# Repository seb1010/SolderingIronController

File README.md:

# Temperature Controller for Hakko 936 Clone

## Overview
 * PID type controller for regulating the temperature of a soldering iron
 * Control done with lm324 quad opamp
 * Heating element switched with back to back mosfets
 * Switching is done only on voltage zero crossings

## Implementation

### PID Controller
 * Fixed Frequency PWM done at about 6 Hz
 * Signal Path
  1. Active Low-Pass Filter / amplifier
  1. Opamp with compenstion network
  1. PWM circuitry
  1. Zero cross detection

#### Active Low-Pass Filter
 * Purpose
   1. Remove a troublesome 60Hz ripple
   1. Increase the small voltage from the thermistor
 * low voltage was a result of low resistance of thermistor and trying to avoid self-heating or using much power
 * gain is 23 v/v for DC
 * 2 poles at about 11 Hz
 
#### Opamp with compenstaion network
  * Gives +50 degrees of phase shift near crossover
  * Has gain magnitude of about 50 v/v at crossover
  * The previous two things come at the cost of significant gain at 60 Hz which caused problems

#### PWM
  * Nothing interesting here
  * An opamp compares output of previous stage to "triangle like" waveform produced by relaxation oscillator

#### Zero Cross Detection
  * Only triggers on rising edge
  * When transformer voltage crosses zero, a short pulse is sent to a latch
  * The pulse allows the latch to change state if such a thing is "requested" by the PWM circuitry
  * The latch drives the gates of the MOSFET's
  * This configuration is not ideal. It works fine for switching MOSFETs on, but do to the inductance of the transformer the zero crossing of the voltage is not at the zero crossing of the current. So there is still some energy stored in the inductor when the swiches open. This didn't cause any real problems, but it would be nice to get this right.

### Switching
 * The Sources of the MOSFETs were connected together
 * This node was also the cicuit ground
   * This made it very easy to switch mosfets
 * The advantages of using MOSFETs
   * Easy to control
   * Low voltage drop results in high efficiency and no need for heat sinking
 * Used a SQ4946AEY Dual MOSFET
 * The gates are intentionally driven through a large resitor to slow switching times

### Power Supply for Control Circuitry
 * Shunt Zener Regulator
   * used a current source in place of usual resitor due to issues caused by 60 Hz ripple on supply rail
 * avoided electrolytic capacitors bc the the case can get quite warm

### PCB
* Had to fit in existing case
* Double sided
* Ordered from prototyping service (JLC PCB)
* I had to hand-solder everything

* Connected to existing case with M3 screws and bits of metal cut from a can
  * This may seem crude, but the board stays in place. Also the can is too flexible to put much stress on the board, so chip capacitors are unlikely to crack.

## Results
 * It seems to provide excellent regulation of the heating element temperature, but in this isn't enough to make a great soldering iron. I believe this system is let down by poor coupling between heating element and  the actual tip.

In the above picture the reference voltage was changed a little and the controller was able to adjust the temperature of the heating element with minimal overshoot in just a few hundred milliseconds. Channel 1 is the Gate Source voltage of the MOSFETs and Channel 2 is the input to the PWM "comparator".

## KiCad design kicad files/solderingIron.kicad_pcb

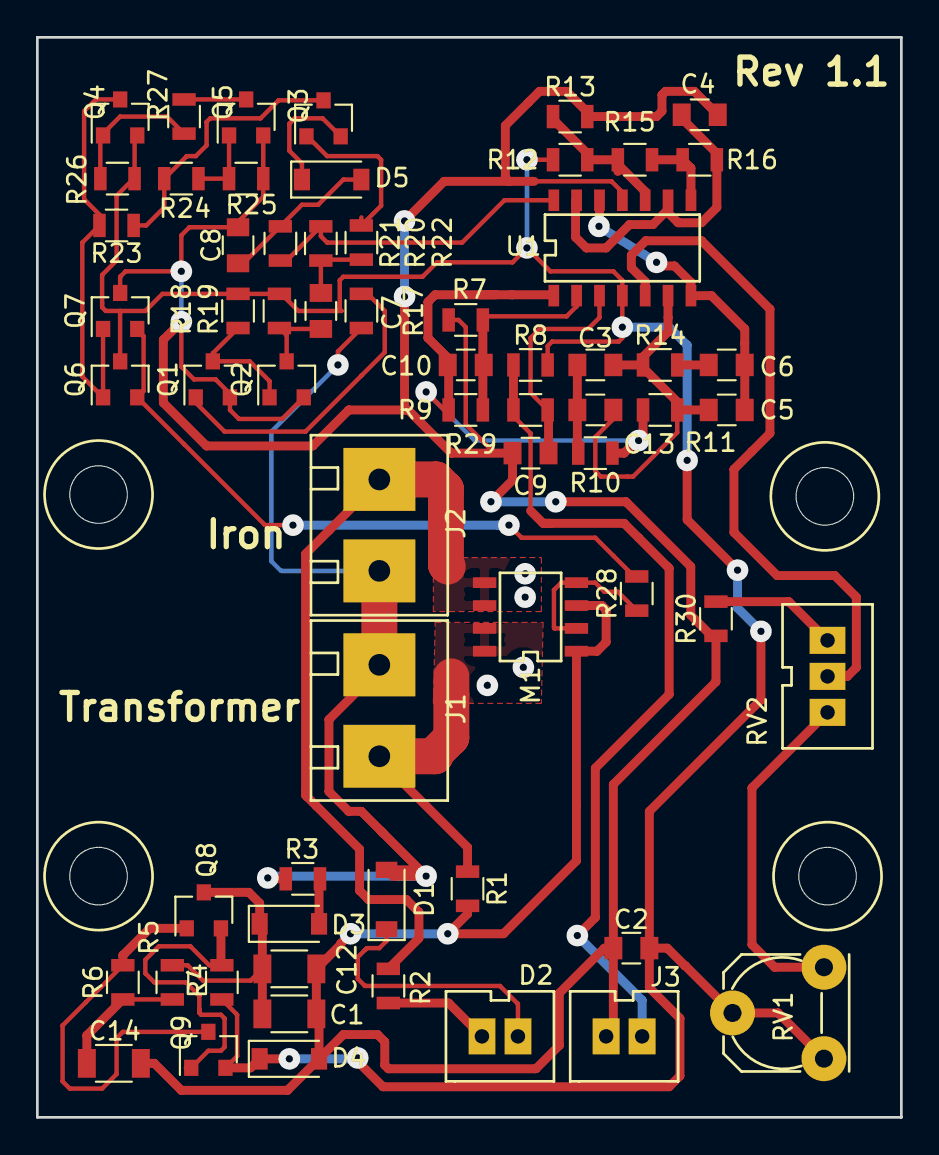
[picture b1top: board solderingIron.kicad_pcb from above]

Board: 2 copper layers, 48.0 x 60.0 mm, 68 parts (0 on the bottom side), 41 nets.

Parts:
C1, C12, C14: 10u; C_1206
C2: 100n; C_0805
C3, C9, C13: 10u; C_0805
C4: 150n; C_0805
C5, C8: 10n; C_0805
C6: 1.5u; C_0805
C7: 220p; C_0805
C10: 68n; C_0805
D1, D3: 1n4003; D_SOD-123
D2: Red; 2.0jst
D4: D_Zener; D_SOD-123
D5: D; D_SOD-123
J1, J2: Conn_01x02; screwTerminal5.08_2
J3: Conn_01x02; 2.0jst
M1: SQ4946AEY; soic_8
MEC1, MEC2, MEC3, MEC4: Screw_Terminal_01x01; m3_hole
Q1, Q2, Q5, Q6, Q8, Q9: MMBT3904; SOT-23
Q3, Q4, Q7: MMBT3906; SOT-23
R1, R2, R17, R18, R19, R21, R26, R27: 100k; R_0805
R3: 100R; R_0805
R4: 120R; R_0805
R5, R6: 33k; R_0805
R7, R30: 10k; R_0805
R8: 5k6; R_0805
R9, R11, R23, R24: 220k; R_0805
R10: 8k2; R_0805
R12, R20: 1M; R_0805
R13: 680k; R_0805
R14: 2M2; R_0805
R15: 150k; R_0805
R16: 470k; R_0805
R22, R28: 56k; R_0805
R25: 68k; R_0805
R29: 1k5; R_0805
RV1: 20k; bluePot
RV2: 10k; jst2.0_3
U1: LM324A; soic_14

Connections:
/Vgate: M1.2, M1.4, R28.1
/Vtrans1: D1.2, J1.2, J2.1, R3.2, R17.2
GND: C1.2, C2.2, C4.1, C8.2, C9.2, C12.2, C14.2, D4.2, J3.1, M1.1, M1.3, Q1.2, Q2.2, Q5.2, Q7.3, R1.2, R7.1, R13.2, R25.2, R30.1, U1.11
unnamed: C1.1, C12.1, D3.1, Q8.3, R5.1
unnamed: C4.2, R16.2, U1.9, U1.13
unnamed: C5.1, C6.1, U1.7, U1.12
unnamed: C6.2, R14.2
unnamed: C7.1, Q2.3, R19.1
unnamed: C7.2, R20.2, R22.1
unnamed: C8.1, D5.2, R21.2
unnamed: C9.1, R29.2, U1.3
unnamed: C10.1, R9.2, R10.1, R11.1, U1.1
unnamed: C10.2, R7.2, R9.1, U1.2
unnamed: C3.1, C13.1, R10.2
unnamed: C3.2, C5.2, C13.2, R11.2, R14.1, U1.6
unnamed: C14.1, R5.2, R6.1
unnamed: D1.1, D2.2
unnamed: D2.1, R2.1
unnamed: D3.2, R3.1
unnamed: D5.1, Q3.2
unnamed: J1.1, M1.7, M1.8, R1.1
unnamed: J2.2, M1.5, M1.6, R2.2
unnamed: J3.2, R8.1, R29.1
unnamed: Q1.1, R17.1
unnamed: Q1.3, Q2.1, R18.1
unnamed: Q3.1, R22.2
unnamed: Q3.3, R23.2, R24.1
unnamed: Q4.1, R26.1, R27.1
unnamed: Q4.3, Q6.1, Q7.1, R23.1
unnamed: Q5.1, R24.2, R25.1
unnamed: Q5.3, R27.2
unnamed: Q6.2, Q7.2, R28.2
unnamed: Q8.1, Q9.3, R6.2
unnamed: Q8.2, Q9.1, R4.2
unnamed: R12.2, R13.1, R15.2, U1.10
unnamed: R15.1, R16.1, U1.8
unnamed: R20.1, R21.1, U1.14
unnamed: R30.2, RV2.3
unnamed: RV1.1, RV2.1
unnamed: RV2.2, U1.5
VCC: C2.1, D4.1, Q4.2, Q6.3, Q9.2, R4.1, R8.2, R12.1, R18.2, R19.2, R26.2, RV1.2, RV1.3, U1.4

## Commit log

2021-07-25 Create LICENSE
2021-07-25 fix readme
2021-07-25 update readme, add images
2021-07-25 adding kicad files
2021-07-25 changing image
2021-07-25 adding image
2021-07-25 fixing image
2021-07-25 typo
2021-07-26 edit Readme, add pdf
2021-07-26 moved files
